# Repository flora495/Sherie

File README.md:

# Sherie
Sherieはオーソリニアな40％キーボードです。

## 組み立て方法
ほとんどの部品は実装済みです。
リセットスイッチとキーソケットだけはんだ付けしてください。
そのあと組み立ててください。

## ファームウェア書き込み
QMK toolboxを使って.hexファイルをキーボードに書き込んでください。QMK MSYSやpromicro web updaterでは書き込めない可能性があります。

## VIA/REMAP
viaのキーマップを書き込んだ上で
jsonファイルは以下を読み込ませることで、via/remapを使用することができます。
qmk_firmware\sherie\keymaps\via\sherie.json 

## コマンド
cd 
`cd /c/Users/F/qmk_firmware/keyboards/sherie`
コンパイル
`qmk compile -kb sherie -km default`
`qmk compile -kb sherie -km via`
フラッシュ(フラッシュはQMK toolboxを使うことを推奨します)
`qmk flash -kb sherie -km default`

## memo

USBとかの周りはGNDベタにしたほうがいいかも。
udb-sのPCBを参照。

## Ref
[1]https://note.com/copkbd/n/n587afde1812e

ATMEGA32U4直付の手順は以下を参照します。
[2]https://wiki.ai03.com/books/pcb-design/chapter/pcb-designer-guide

[3]https://taro-hayashi.github.io/LetsMakeaKeypadWithAtmega32u2/

typeC周りの回路
[4]https://github.com/Unified-Daughterboard/UDB-S

静電気対策（特に金属ケースの場合は参照）
[5]https://gist.github.com/s-show/286ffb1f5d9c886b514ff7a37e6d8d37

ベタGNDとか
[6]https://taro-hayashi.github.io/LetsMakeaKeypadWithAtmega32u2/

[7]https://qiita.com/Sugimoto_Yuuki/items/860ca6a57c2501f1cbab

[8]https://docs.qmk.fm/driver_installation_zadig

## バグ
QMK MSYSでflashできない場合
以下のようなエラーが出てflashに失敗する場合があります。

<br>
これは実はエラーができても書き込み自体はできているっぽいです。
<br>
エラーなく書き込みたい場合は、QMK Toolboxを使って書き込みます。
<br>
エラーの原因はよくわからないが、おそらくポートのデバイスではなくてUSBデバイスとして認識しているのが原因。
<br>
おそらくですが、USBのドライバーが原因でした。[7]を参照し、ドライバーをWinUSBに書き換えます。こうするとQMK toolboxでエラーなしで読み込むことができるようになりました。
ただし、winUSBにするとQMK MSYSではflashできないぽいです。
ちなみにドライバーを変えるとシリアルポートで認識するようにもでるようにもできるっぽいです。
ただ、[8]によると、atmega32uの推奨driverはwinUSBなので、大人しく従う方がいいと思います。

## 改良点
1. 真ん中にネジ穴追加
1. スタビライザーのネジ穴のワッシャー分もボトムプレートの範囲を広げる
1. 電源のLEDが明るすぎる。暗くするのと、ジャンパでLEDを接続しないこともできるようにする
1. ブートローダー書き込みモードのときに光るLEDを追加する。
1. 1.5uのキーにもスタビライザーを追加？

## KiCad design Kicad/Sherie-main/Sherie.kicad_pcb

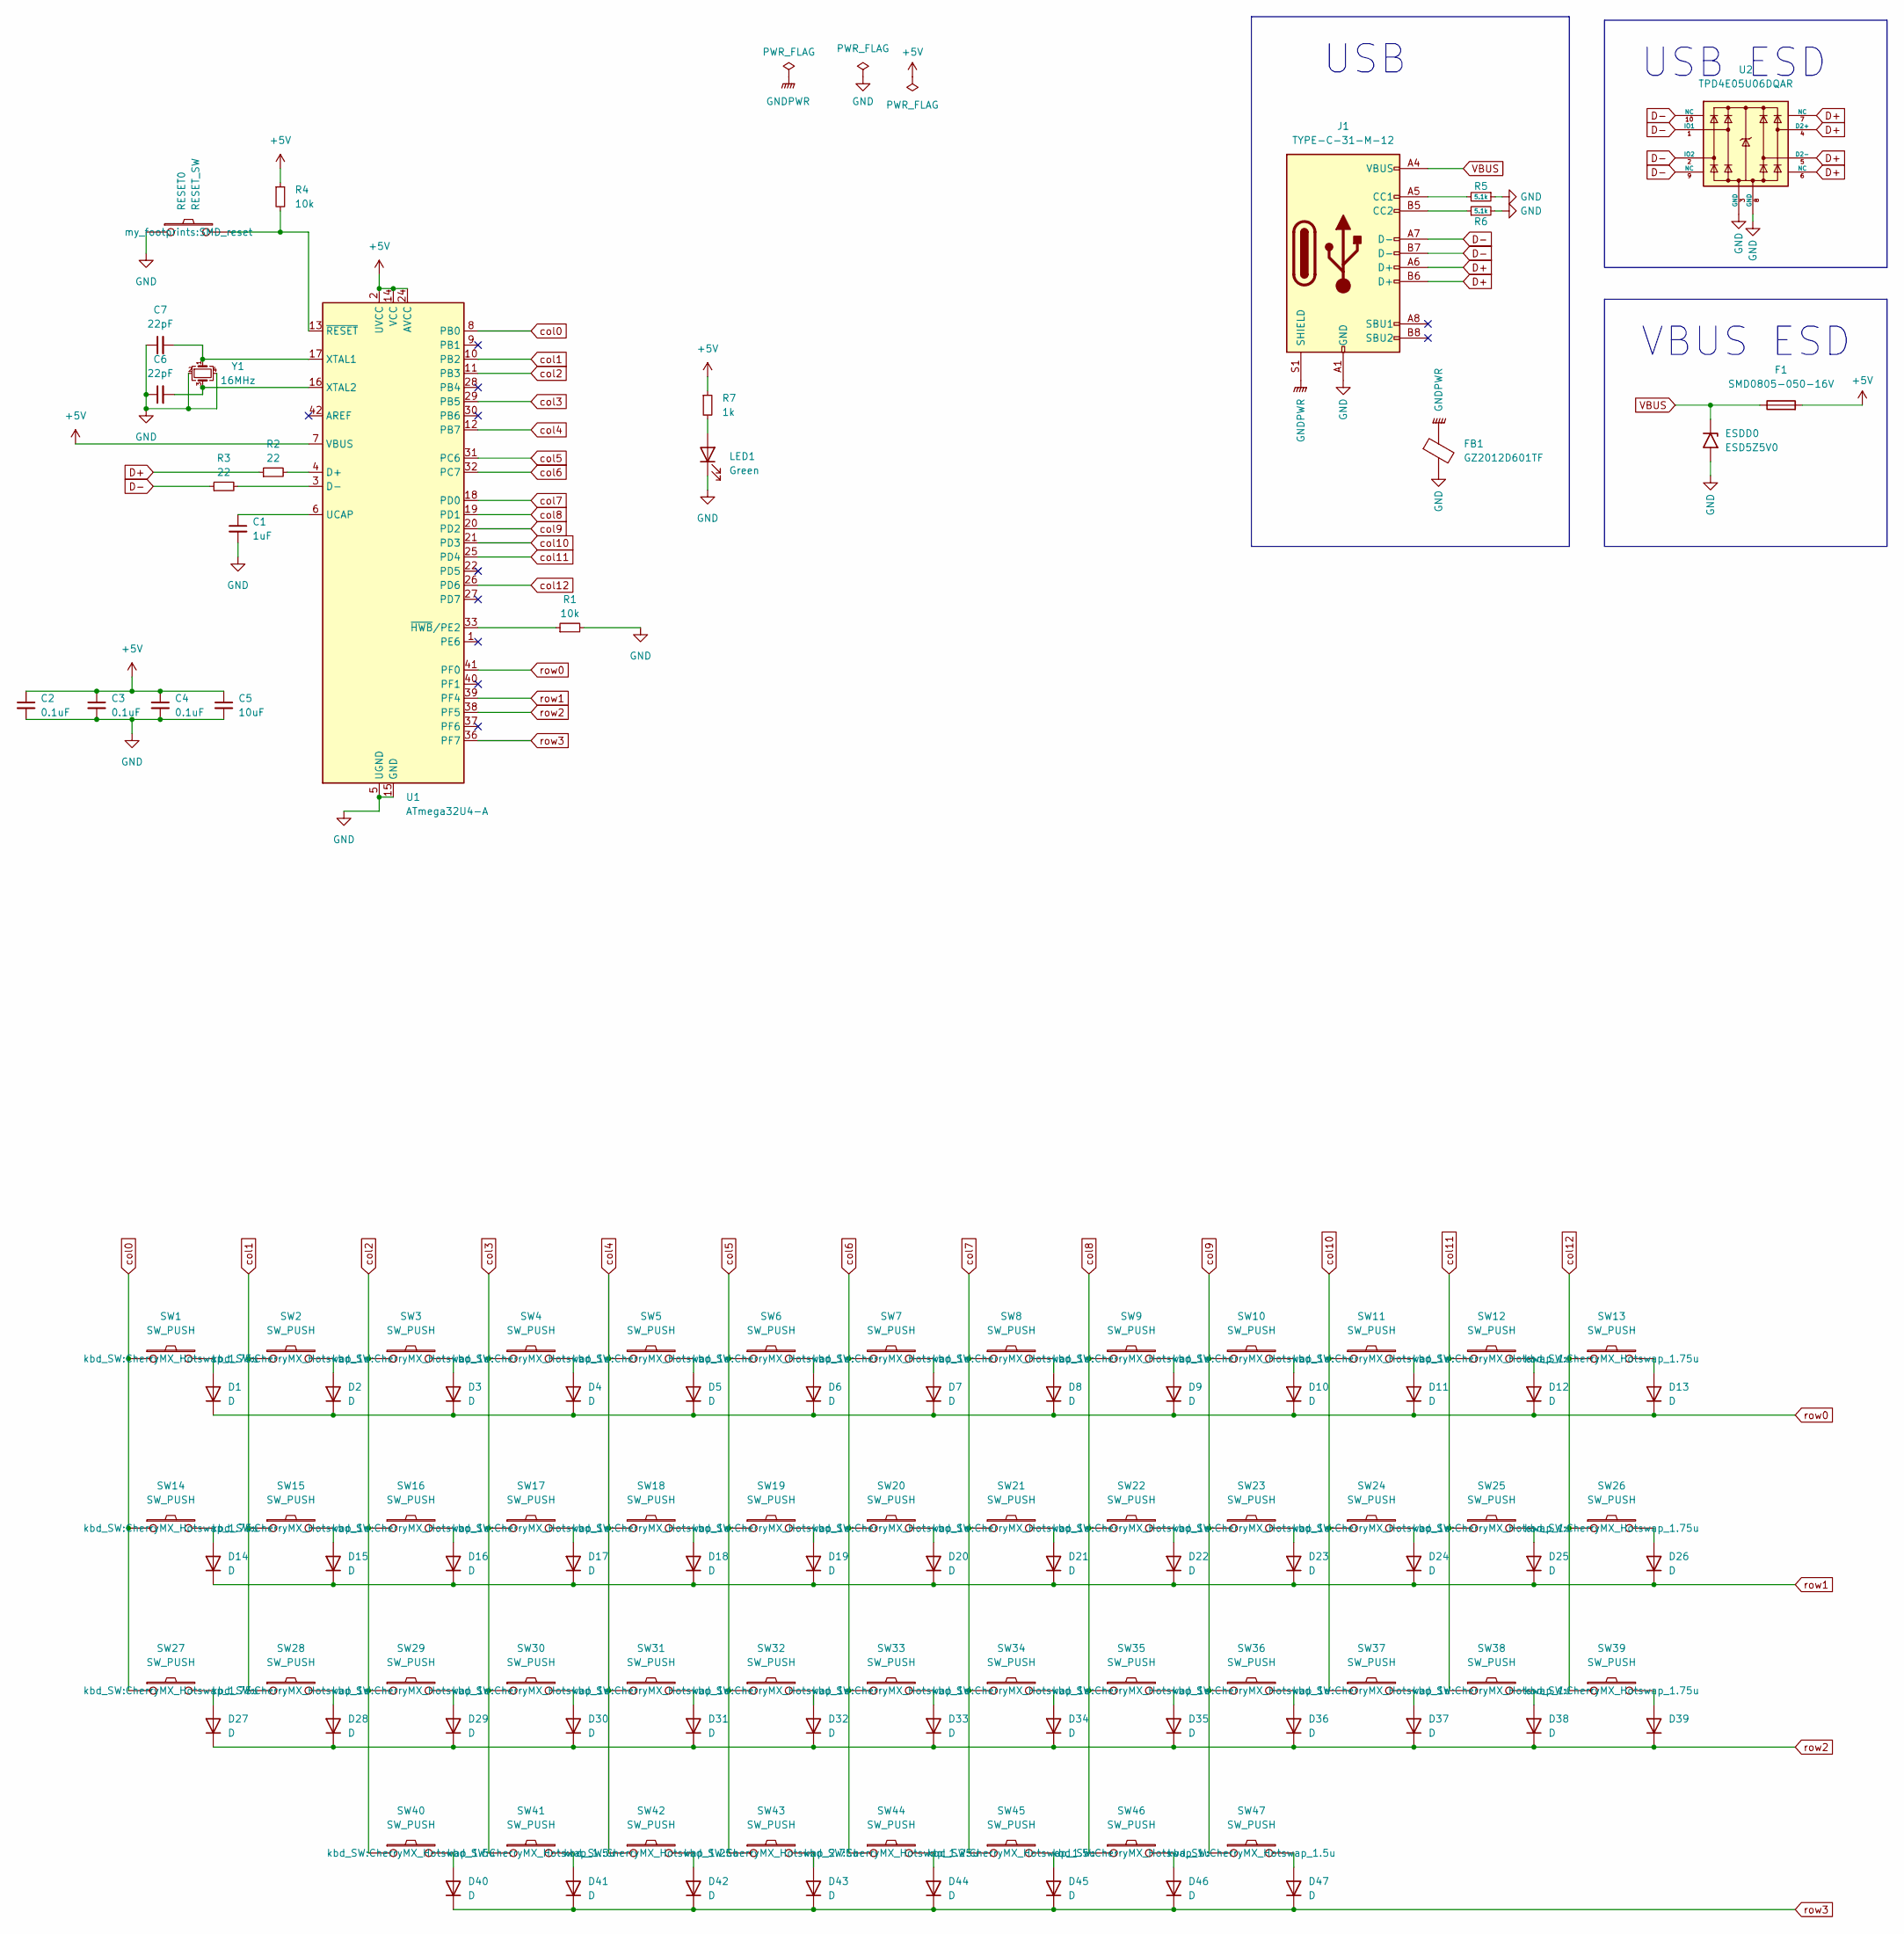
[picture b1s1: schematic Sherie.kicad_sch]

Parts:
C1: 1uF; C_0805_2012Metric
C2, C3, C4: 0.1uF; C_0805_2012Metric
C5: 10uF; C_0805_2012Metric
C6, C7: 22pF; C_0805_2012Metric
D1, D2, D3, D4, D5, D6, D7, D8, D9, D10, D11, D12, D13, D14, D15, D16, D17, D18, D19, D20, D21, D22, D23, D24, D25, D26, D27, D28, D29, D30, D31, D32, D33, D34, D35, D36, D37, D38, D39, D40, D41, D42, D43, D44, D45, D46, D47: D; Diode_TH_SMD_without_holes
ESDD0: ESD5Z5V0; D_SOD-523; Manufacturer Part Number ESD5Z5V0; LCSC Part Number C502546
F1: SMD0805-050-16V; Fuse_1206_3216Metric; Manufacturer Part Number SMD0805-050-16V; LCSC Part Number C2833485
FB1: GZ2012D601TF; L_0805_2012Metric; Manufacturer Part Number GZ2012D601TF; LCSC Part Number C1017
J1: TYPE-C-31-M-12; HRO-TYPE-C-31-M-12-Assembly; Manufacturer Part Number TYPE-C-31-M-12; LCSC Part Number C165948
LED1: Green; LED0805-RD_GREEN
R1, R4: 10k; R_0805_2012Metric
R2, R3: 22; R_0805_2012Metric
R5, R6: 5.1k; R_0805_2012Metric
R7: 1k; R_0805_2012Metric
RESET0: RESET_SW; SMD_reset
SW1, SW13, SW14, SW26, SW27, SW39: SW_PUSH; CherryMX_Hotswap_1.75u
SW2, SW3, SW4, SW5, SW6, SW7, SW8, SW9, SW10, SW11, SW12, SW15, SW16, SW17, SW18, SW19, SW20, SW21, SW22, SW23, SW24, SW25, SW28, SW29, SW30, SW31, SW32, SW33, SW34, SW35, SW36, SW37, SW38, SW46: SW_PUSH; CherryMX_Hotswap_1u
SW40, SW41, SW45, SW47: SW_PUSH; CherryMX_Hotswap_1.5u
SW42, SW44: SW_PUSH; CherryMX_Hotswap_1.25u
SW43: SW_PUSH; CherryMX_Hotswap_2.75u
U1: ATmega32U4-A; TQFP-44_10x10mm_P0.8mm
U2: TPD4E05U06DQAR; USON-10_2.5x1.0mm_P0.5mm; Manufacturer Part Number TPD4E05U06DQAR; LCSC Part Number C2836386
Y1: 16MHz; Crystal_SMD_3225-4Pin_3.2x2.5mm

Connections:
+5V: C2.1, C3.1, C4.1, C5.1, F1.2, R4.1, R7.1, U1.2 (UVCC), U1.7 (VBUS), U1.14 (VCC), U1.24 (AVCC), U1.34 (VCC), U1.44 (AVCC)
D+: J1.A6 (D+), J1.B6 (D+), R2.1, U2.4 (D2+), U2.5 (D2-), U2.6 (NC), U2.7 (NC)
D-: J1.A7 (D-), J1.B7 (D-), R3.1, U2.1 (IO1), U2.2 (IO2), U2.9 (NC), U2.10 (NC)
GND: C1.2, C2.2, C3.2, C4.2, C5.2, C6.1, C7.1, ESDD0.2 (A2), FB1.2, J1.A1 (GND), J1.A12 (GND), J1.B1 (GND), J1.B12 (GND), LED1.1 (K), R1.2, R5.1, R6.2, RESET0.1, U1.5 (UGND), U1.15 (GND), U1.23 (GND), U1.35 (GND), U1.43 (GND), U2.3 (GND), U2.8 (GND), Y1.2, Y1.4
GNDPWR: FB1.1, J1.S1 (SHIELD)
unnamed: D1.2 (A), SW1.2
unnamed: D2.2 (A), SW2.2
unnamed: D3.2 (A), SW3.2
unnamed: D4.2 (A), SW4.2
unnamed: D5.2 (A), SW5.2
unnamed: D6.2 (A), SW6.2
unnamed: D7.2 (A), SW7.2
unnamed: D8.2 (A), SW8.2
unnamed: D9.2 (A), SW9.2
unnamed: D10.2 (A), SW10.2
unnamed: D11.2 (A), SW11.2
unnamed: D12.2 (A), SW12.2
unnamed: D13.2 (A), SW13.2
unnamed: D14.2 (A), SW14.2
unnamed: D15.2 (A), SW15.2
unnamed: D16.2 (A), SW16.2
unnamed: D17.2 (A), SW17.2
unnamed: D18.2 (A), SW18.2
unnamed: D19.2 (A), SW19.2
unnamed: D20.2 (A), SW20.2
unnamed: D21.2 (A), SW21.2
unnamed: D22.2 (A), SW22.2
unnamed: D23.2 (A), SW23.2
unnamed: D24.2 (A), SW24.2
unnamed: D25.2 (A), SW25.2
unnamed: D26.2 (A), SW26.2
unnamed: D27.2 (A), SW27.2
unnamed: D28.2 (A), SW28.2
unnamed: D29.2 (A), SW29.2
unnamed: D30.2 (A), SW30.2
unnamed: D31.2 (A), SW31.2
unnamed: D32.2 (A), SW32.2
unnamed: D33.2 (A), SW33.2
unnamed: D34.2 (A), SW34.2
unnamed: D35.2 (A), SW35.2
unnamed: D36.2 (A), SW36.2
unnamed: D37.2 (A), SW37.2
unnamed: D38.2 (A), SW38.2
unnamed: D39.2 (A), SW39.2
unnamed: D40.2 (A), SW40.2
unnamed: D41.2 (A), SW41.2
unnamed: D42.2 (A), SW42.2
unnamed: D43.2 (A), SW43.2
unnamed: D44.2 (A), SW44.2
unnamed: D45.2 (A), SW45.2
unnamed: D46.2 (A), SW46.2
unnamed: D47.2 (A), SW47.2
unnamed: J1.A5 (CC1), R5.2
unnamed: J1.B5 (CC2), R6.1
unnamed: LED1.2 (A), R7.2
unnamed: R2.2, U1.4 (D+)
unnamed: R3.2, U1.3 (D-)
unnamed: C1.1, U1.6 (UCAP)
unnamed: C7.2, U1.17 (XTAL1), Y1.1
unnamed: C6.2, U1.16 (XTAL2), Y1.3
unnamed: R1.1, U1.33 (~HWB/PE2)
unnamed: R4.2, RESET0.2, U1.13 (~RESET)
VBUS: ESDD0.1 (A1), F1.1, J1.A4 (VBUS), J1.A9 (VBUS), J1.B4 (VBUS), J1.B9 (VBUS)
col0: SW1.1, SW14.1, SW27.1, U1.8 (PB0)
col1: SW2.1, SW15.1, SW28.1, U1.10 (PB2)
col2: SW3.1, SW16.1, SW29.1, SW40.1, U1.11 (PB3)
col3: SW4.1, SW17.1, SW30.1, SW41.1, U1.29 (PB5)
col4: SW5.1, SW18.1, SW31.1, SW42.1, U1.12 (PB7)
col5: SW6.1, SW19.1, SW32.1, SW43.1, U1.31 (PC6)
col6: SW7.1, SW20.1, SW33.1, SW44.1, U1.32 (PC7)
col7: SW8.1, SW21.1, SW34.1, SW45.1, U1.18 (PD0)
col8: SW9.1, SW22.1, SW35.1, SW46.1, U1.19 (PD1)
col9: SW10.1, SW23.1, SW36.1, SW47.1, U1.20 (PD2)
col10: SW11.1, SW24.1, SW37.1, U1.21 (PD3)
col11: SW12.1, SW25.1, SW38.1, U1.25 (PD4)
col12: SW13.1, SW26.1, SW39.1, U1.26 (PD6)
row0: D1.1 (K), D2.1 (K), D3.1 (K), D4.1 (K), D5.1 (K), D6.1 (K), D7.1 (K), D8.1 (K), D9.1 (K), D10.1 (K), D11.1 (K), D12.1 (K), D13.1 (K), U1.41 (PF0)
row1: D14.1 (K), D15.1 (K), D16.1 (K), D17.1 (K), D18.1 (K), D19.1 (K), D20.1 (K), D21.1 (K), D22.1 (K), D23.1 (K), D24.1 (K), D25.1 (K), D26.1 (K), U1.39 (PF4)
row2: D27.1 (K), D28.1 (K), D29.1 (K), D30.1 (K), D31.1 (K), D32.1 (K), D33.1 (K), D34.1 (K), D35.1 (K), D36.1 (K), D37.1 (K), D38.1 (K), D39.1 (K), U1.38 (PF5)
row3: D40.1 (K), D41.1 (K), D42.1 (K), D43.1 (K), D44.1 (K), D45.1 (K), D46.1 (K), D47.1 (K), U1.36 (PF7)

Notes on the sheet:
USB
USB ESD
VBUS ESD

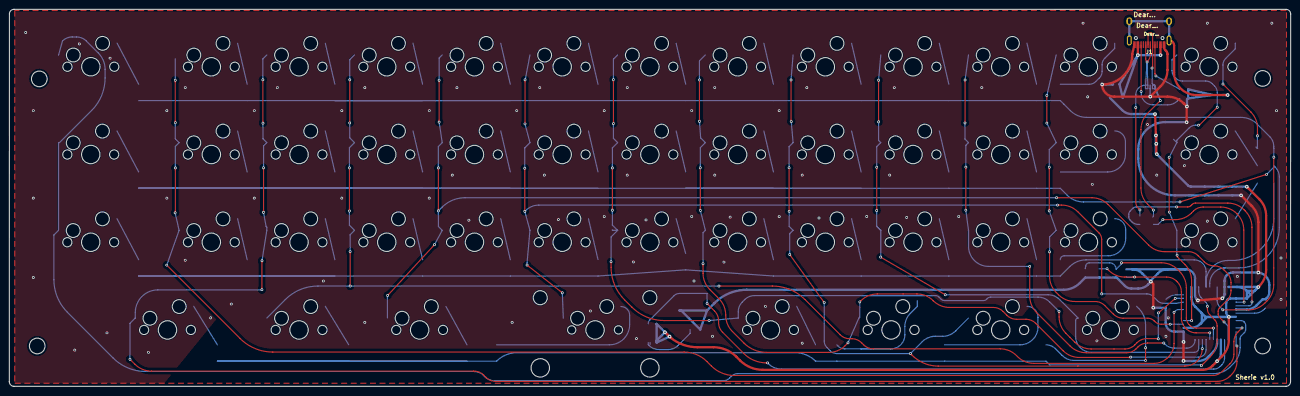
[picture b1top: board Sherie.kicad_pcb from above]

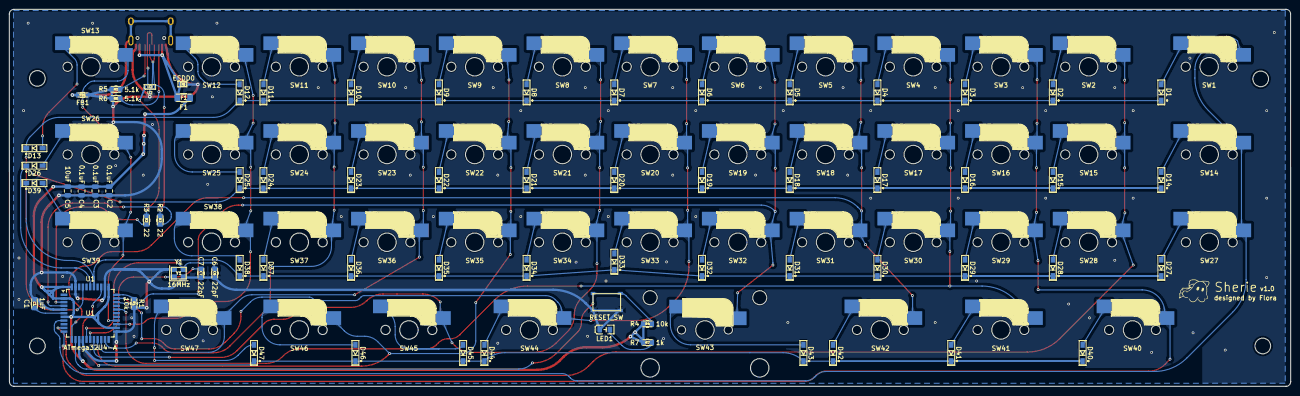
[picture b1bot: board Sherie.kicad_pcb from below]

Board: 2 copper layers, 278.3 x 81.9 mm, 117 parts (22 on the bottom side), 80 nets.

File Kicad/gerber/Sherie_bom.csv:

Reference,Value,Datasheet,Footprint,Qty,DNP
U2,TPD4E05U06DQAR,,acheron_Components:USON-10_2.5x1.0mm_P0.5mm,1,
C1,1uF,~,Capacitor_SMD:C_0805_2012Metric,1,
"C2,C3,C4",0.1uF,~,Capacitor_SMD:C_0805_2012Metric,3,
C5,10uF,~,Capacitor_SMD:C_0805_2012Metric,1,
"C6,C7",22pF,~,Capacitor_SMD:C_0805_2012Metric,2,
Y1,16MHz,~,Crystal:Crystal_SMD_3225-4Pin_3.2x2.5mm,1,
ESDD0,ESD5Z5V0,https://www.vishay.com/doc?85881,Diode_SMD:D_SOD-523,1,
F1,SMD0805-050-16V,~,Fuse:Fuse_1206_3216Metric,1,
FB1,GZ2012D601TF,~,Inductor_SMD:L_0805_2012Metric,1,
"D1,D2,D3,D4,D5,D6,D7,D8,D9,D10,D11,D12,D13,D14,D15,D16,D17,D18,D19,D20,D21,D22,D23,D24,D25,D26,D27,D28,D29,D30,D31,D32,D33,D34,D35,D36,D37,D38,D39,D40,D41,D42,D43,D44,D45,D46,D47",D,~,kbd_Parts:Diode_TH_SMD_without_holes,47,
LED1,Green,~,my_footprints:LED0805-RD_GREEN,1,
U1,ATmega32U4-A,http://ww1.microchip.com/downloads/en/DeviceDoc/Atmel-7766-8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,Package_QFP:TQFP-44_10x10mm_P0.8mm,1,
"R1,R4",10k,~,Resistor_SMD:R_0805_2012Metric,2,
"R2,R3",22,~,Resistor_SMD:R_0805_2012Metric,2,
"R5,R6",5.1k,~,Resistor_SMD:R_0805_2012Metric,2,
R7,1k,~,Resistor_SMD:R_0805_2012Metric,1,

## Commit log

2024-06-24 v1.0完成
2024-07-03 色々コミット
2024-07-03 readmeを追記
2024-07-07 reamp対応など
2024-07-07 README.mdを更新
2024-10-07 iroiro
